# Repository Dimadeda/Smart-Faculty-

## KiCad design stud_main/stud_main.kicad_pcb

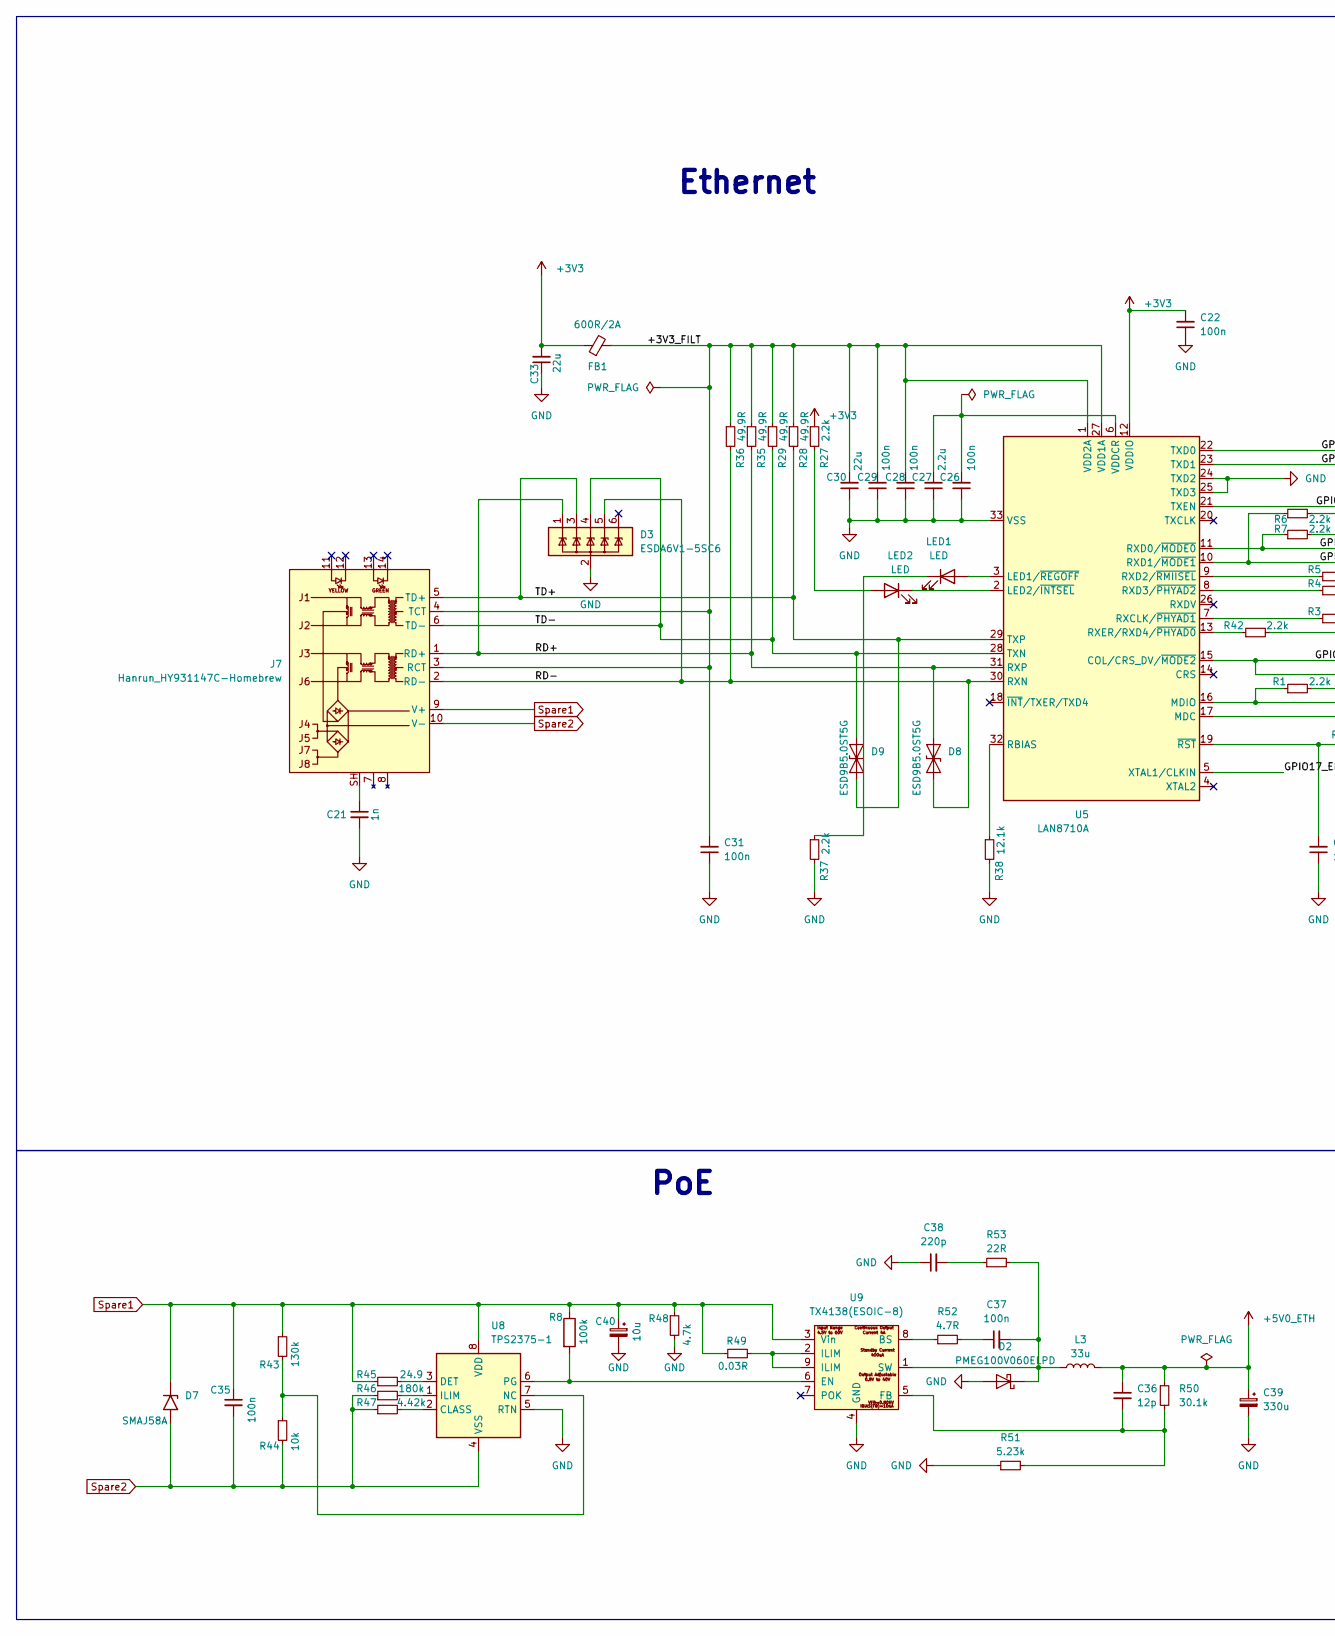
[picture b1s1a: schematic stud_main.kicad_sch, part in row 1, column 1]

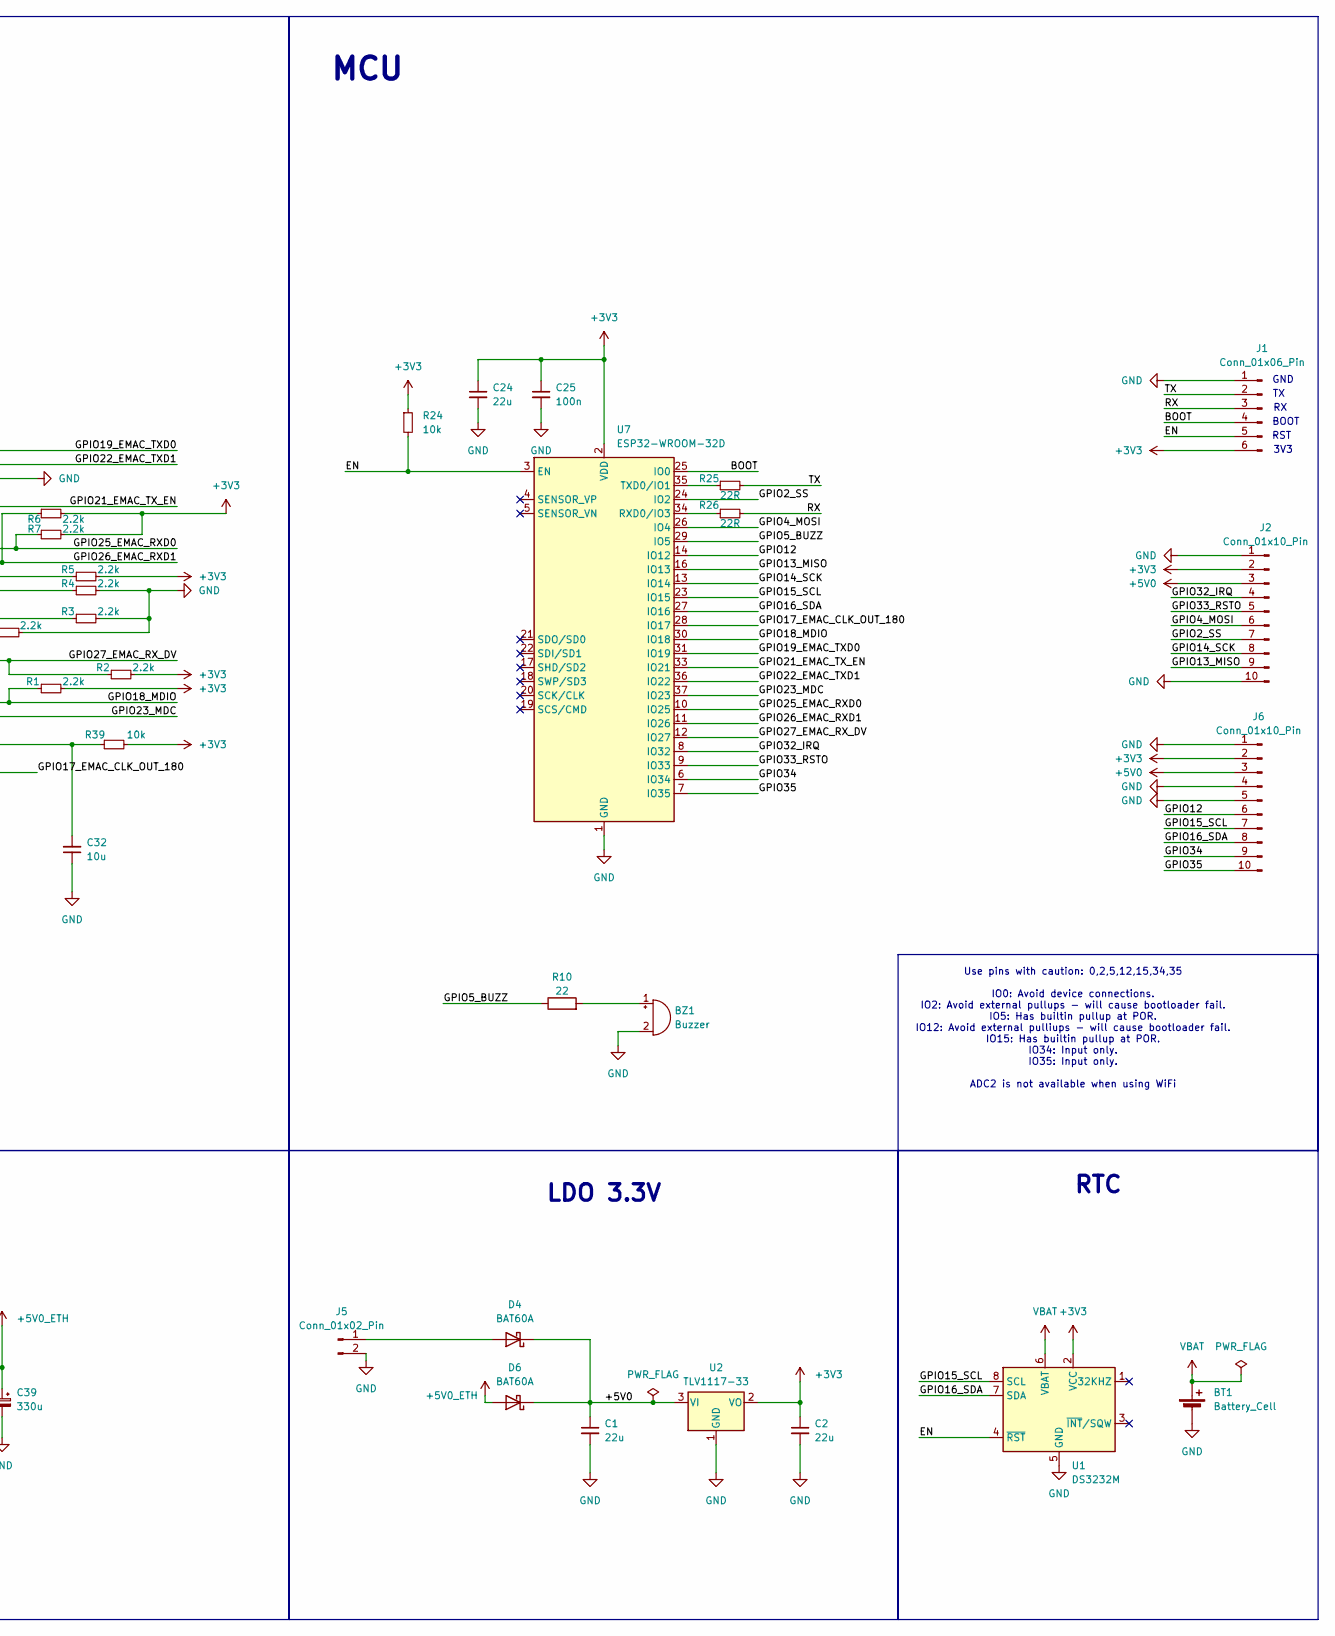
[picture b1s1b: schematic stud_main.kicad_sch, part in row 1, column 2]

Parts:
BT1: Battery_Cell; BatteryHolder_Keystone_1060_1x2032
BZ1: Buzzer; Buzzer_12x9.5RM7.6
C1, C2, C24, C30, C33: 22u; C_0805_2012Metric_Pad1.18x1.45mm_HandSolder
C21: 1n; C_0805_2012Metric_Pad1.18x1.45mm_HandSolder
C22, C25, C26, C28, C29, C35, C37: 100n; C_0805_2012Metric
C27: 2.2u; C_0805_2012Metric_Pad1.18x1.45mm_HandSolder
C31: 100n; C_0805_2012Metric_Pad1.18x1.45mm_HandSolder
C32: 10u; C_0805_2012Metric_Pad1.18x1.45mm_HandSolder
C36: 12p; C_0805_2012Metric_Pad1.18x1.45mm_HandSolder
C38: 220p; C_0805_2012Metric_Pad1.18x1.45mm_HandSolder
C39: 330u; CP_EIA-7343-30_AVX-N_Pad2.25x2.55mm_HandSolder
C40: 10u; C_1210_3225Metric
D2: PMEG100V060ELPD; Nexperia_CFP15_SOT-1289
D3: ESDA6V1-5SC6; SOT-23-6
D4, D6: BAT60A; D_SOD-323
D7: SMAJ58A; D_SMA
D8, D9: ESD9B5.0ST5G; D_SOD-923
FB1: 600R/2A; L_0805_2012Metric
J1: Conn_01x06_Pin; PinHeader_1x06_P2.54mm_Vertical
J2, J6: Conn_01x10_Pin; PinHeader_1x10_P2.54mm_Vertical
J5: Conn_01x02_Pin; PinHeader_1x02_P2.54mm_Vertical
J7: Hanrun_HY931147C-Homebrew; RJ45_Hanrun_HY934711C
L3: 33u; L_Sumida_CDMC6D28_7.25x6.5mm
LED1, LED2: LED; LED_0805_2012Metric
R1, R2, R3, R4, R5, R6, R7, R27, R37, R42: 2.2k; R_0805_2012Metric_Pad1.20x1.40mm_HandSolder
R8: 100k; R_0805_2012Metric_Pad1.20x1.40mm_HandSolder
R10: 22; R_0805_2012Metric
R24, R39, R44: 10k; R_0805_2012Metric_Pad1.20x1.40mm_HandSolder
R25, R26, R53: 22R; R_0805_2012Metric_Pad1.20x1.40mm_HandSolder
R28, R29, R35, R36: 49.9R; R_0805_2012Metric_Pad1.20x1.40mm_HandSolder
R38: 12.1k; R_0805_2012Metric_Pad1.20x1.40mm_HandSolder
R43: 130k; R_0805_2012Metric_Pad1.20x1.40mm_HandSolder
R45: 24.9; R_0805_2012Metric_Pad1.20x1.40mm_HandSolder
R46: 180k; R_0805_2012Metric_Pad1.20x1.40mm_HandSolder
R47: 4.42k; R_0805_2012Metric_Pad1.20x1.40mm_HandSolder
R48: 4.7k; R_1812_4532Metric_Pad1.30x3.40mm_HandSolder
R49: 0.03R; R_1206_3216Metric_Pad1.30x1.75mm_HandSolder
R50: 30.1k; R_0805_2012Metric_Pad1.20x1.40mm_HandSolder
R51: 5.23k; R_0805_2012Metric_Pad1.20x1.40mm_HandSolder
R52: 4.7R; R_0805_2012Metric_Pad1.20x1.40mm_HandSolder
U1: DS3232M; SOIC-8_3.9x4.9mm_P1.27mm
U2: TLV1117-33; SOT-223-3_TabPin2
U5: LAN8710A; QFN-32-1EP_5x5mm_P0.5mm_EP3.3x3.3mm_ThermalVias
U7: ESP32-WROOM-32D
U8: TPS2375-1; TSSOP-8_4.4x3mm_P0.65mm
U9: TX4138(ESOIC-8); SOIC-8-1EP_3.9x4.9mm_P1.27mm_EP2.41x3.3mm

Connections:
+3V3: C2.1, C22.2, C24.1, C25.1, C33.2, FB1.1, J1.6, J2.2, J6.2, R1.2, R2.2, R5.2, R6.2, R7.2, R24.1, R27.1, R39.2, U1.2 (VCC), U2.2 (VO), U5.12 (VDDIO), U7.2 (VDD)
+5V0: C1.1, D4.1 (K), D6.1 (K), J2.3, J6.3, U2.3 (VI)
+5V0_ETH: C36.1, C39.1, D6.2 (A), L3.2, R50.1
/+3V3_FILT: C28.2, C29.2, C30.2, C31.2, FB1.2, J7.3 (RCT), J7.4 (TCT), R28.1, R29.1, R35.1, R36.1, U5.1 (VDD2A), U5.27 (VDD1A)
/BOOT: J1.4, U7.25 (IO0)
/EN: J1.5, R24.2, U1.4 (~RST), U7.3 (EN)
/GPIO2_SS: J2.7, U7.24 (IO2)
/GPIO4_MOSI: J2.6, U7.26 (IO4)
/GPIO5_BUZZ: R10.1, U7.29 (IO5)
/GPIO12: J6.6, U7.14 (IO12)
/GPIO13_MISO: J2.9, U7.16 (IO13)
/GPIO14_SCK: J2.8, U7.13 (IO14)
/GPIO15_SCL: J6.7, U1.8 (SCL), U7.23 (IO15)
/GPIO16_SDA: J6.8, U1.7 (SDA), U7.27 (IO16)
/GPIO17_EMAC_CLK_OUT_180: U5.5 (XTAL1/CLKIN), U7.28 (IO17)
/GPIO18_MDIO: R1.1, U5.16 (MDIO), U7.30 (IO18)
/GPIO19_EMAC_TXD0: U5.22 (TXD0), U7.31 (IO19)
/GPIO21_EMAC_TX_EN: U5.21 (TXEN), U7.33 (IO21)
/GPIO22_EMAC_TXD1: U5.23 (TXD1), U7.36 (IO22)
/GPIO23_MDC: U5.17 (MDC), U7.37 (IO23)
/GPIO25_EMAC_RXD0: R7.1, U5.11 (RXD0/~MODE0), U7.10 (IO25)
/GPIO26_EMAC_RXD1: R6.1, U5.10 (RXD1/~MODE1), U7.11 (IO26)
/GPIO27_EMAC_RX_DV: R2.1, U5.15 (COL/CRS_DV/~MODE2), U7.12 (IO27)
/GPIO32_IRQ: J2.4, U7.8 (IO32)
/GPIO33_RSTO: J2.5, U7.9 (IO33)
/GPIO34: J6.9, U7.6 (IO34)
/GPIO35: J6.10, U7.7 (IO35)
/RD+: D3.1 (IO1), D8.2 (A2), J7.1 (RD+), R35.2, U5.31 (RXP)
/RD-: D3.5 (IO4), D8.1 (A1), J7.2 (RD-), R36.2, U5.30 (RXN)
/RX: J1.3, R26.2
/TD+: D3.3 (IO2), D9.2 (A2), J7.5 (TD+), R28.2, U5.29 (TXP)
/TD-: D3.4 (IO3), D9.1 (A1), J7.6 (TD-), R29.2, U5.28 (TXN)
/TX: J1.2, R25.2
GND: BT1.2 (-), BZ1.2 (-), C1.2, C2.2, C21.2, C22.1, C24.2, C25.2, C26.1, C27.1, C28.1, C29.1, C30.1, C31.1, C32.1, C33.1, C38.1, C39.2, C40.2, D2.1 (A), D2.2 (A), D3.2 (GND), J1.1, J2.1, J2.10, J5.2, J6.1, J6.4, J6.5, R3.2, R4.2, R37.2, R38.2, R42.2, R48.2, R51.1, U1.5 (GND), U2.1 (GND), U5.24 (TXD2), U5.25 (TXD3), U5.33 (VSS), U7.1 (GND), U7.15 (GND), U7.38 (GND), U7.39 (GND), U8.5 (RTN), U9.4 (GND)
unnamed: BZ1.1 (+), R10.2
unnamed: C21.1, J7.SH
unnamed: C37.1, R52.2
unnamed: C38.2, R53.1
unnamed: C37.2, D2.3 (K), L3.1, R53.2, U9.1 (SW)
unnamed: D4.2 (A), J5.1
unnamed: LED1.2 (A), U5.3 (LED1/~REGOFF)
unnamed: LED1.1 (K), R37.1
unnamed: LED2.2 (A), R27.2
unnamed: LED2.1 (K), U5.2 (LED2/~INTSEL)
unnamed: R49.2, U9.2 (ILIM), U9.9 (ILIM)
unnamed: R38.1, U5.32 (RBIAS)
unnamed: R3.1, U5.7 (RXCLK/~PHYAD1)
unnamed: R5.1, U5.9 (RXD2/~RMIISEL)
unnamed: R4.1, U5.8 (RXD3/~PHYAD2)
unnamed: R42.1, U5.13 (RXER/RXD4/~PHYAD0)
unnamed: C26.2, C27.2, U5.6 (VDDCR)
unnamed: C32.2, R39.1, U5.19 (~RST)
unnamed: R26.1, U7.34 (RXD0/IO3)
unnamed: R25.1, U7.35 (TXD0/IO1)
unnamed: R47.2, U8.2 (CLASS)
unnamed: R45.2, U8.3 (DET)
unnamed: R46.2, U8.1 (ILIM)
unnamed: R43.2, R44.1, U8.7 (NC)
unnamed: R8.2, U8.6 (PG), U9.6 (EN)
unnamed: R52.1, U9.8 (BS)
unnamed: C36.2, R50.2, R51.2, U9.5 (FB)
Spare1: C35.1, C40.1, D7.1 (A1), J7.9 (V+), R8.1, R43.1, R45.1, R48.1, R49.1, U8.8 (VDD), U9.3 (Vin)
Spare2: C35.2, D7.2 (A2), J7.10 (V-), R44.2, R46.1, R47.1, U8.4 (VSS)
VBAT: BT1.1 (+), U1.6 (VBAT)

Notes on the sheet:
3V3
BOOT
Use pins with caution: 0,2,5,12,15,34,35 IO0: Avoid device connections. IO2: Avoid external pullups - will cause bootloader fail. IO5: Has builtin pullup at POR. IO12: Avoid external pulliups - will cause bootloader fail. IO15: Has builtin pullup at POR. IO34: Input only. IO35: Input only. ADC2 is 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
RST
MCU
Ethernet
GND
LDO 3.3V
RTC
PoE

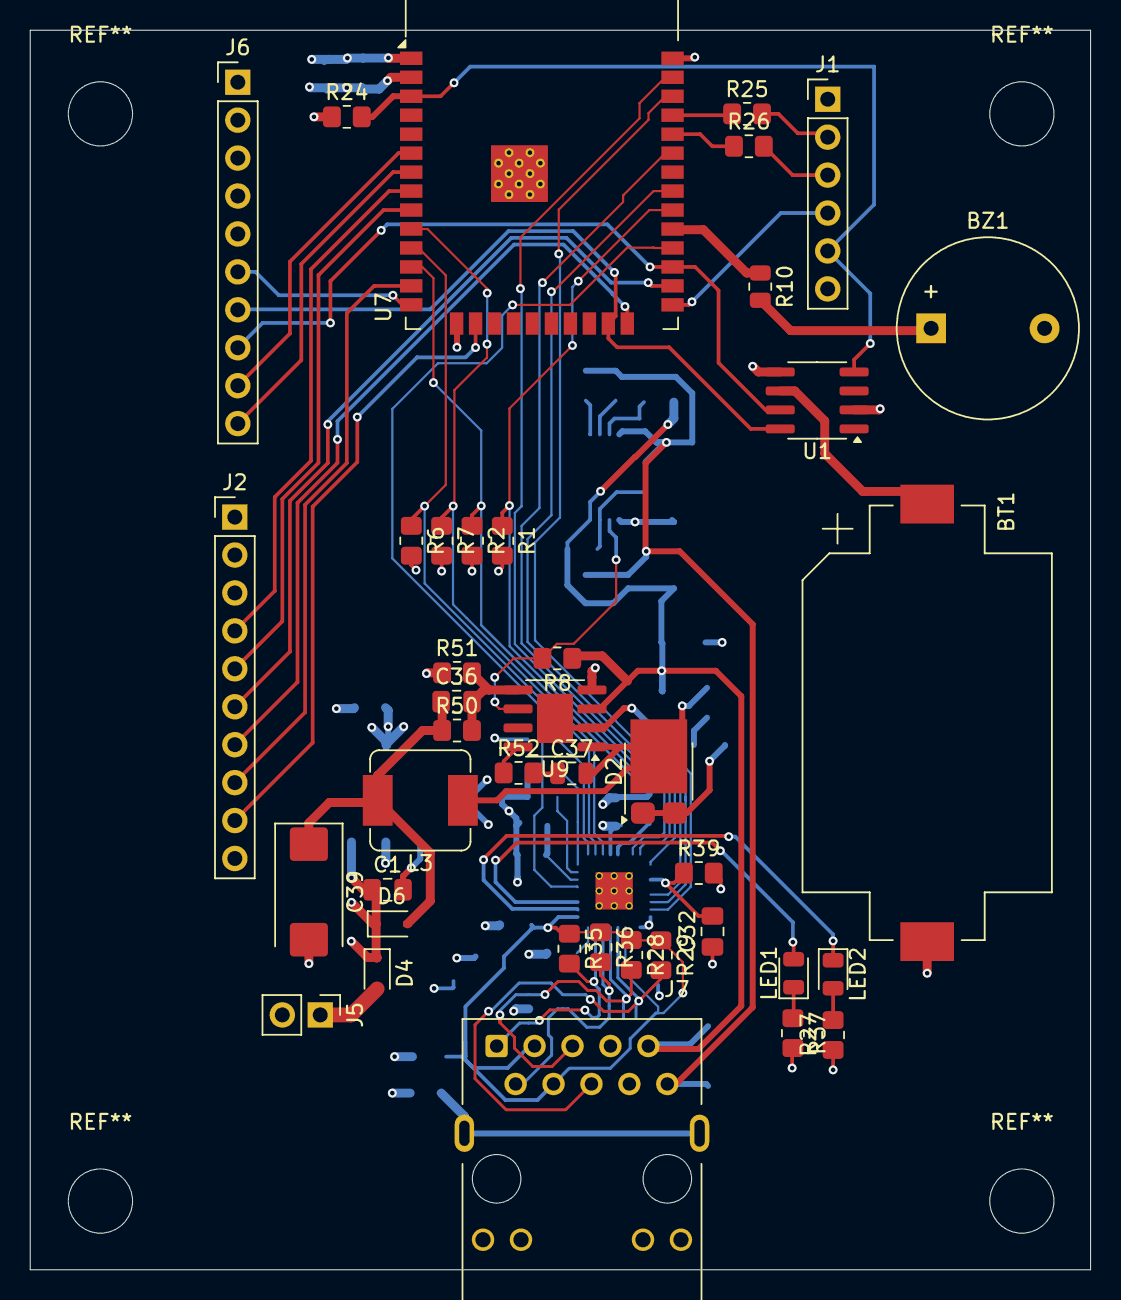
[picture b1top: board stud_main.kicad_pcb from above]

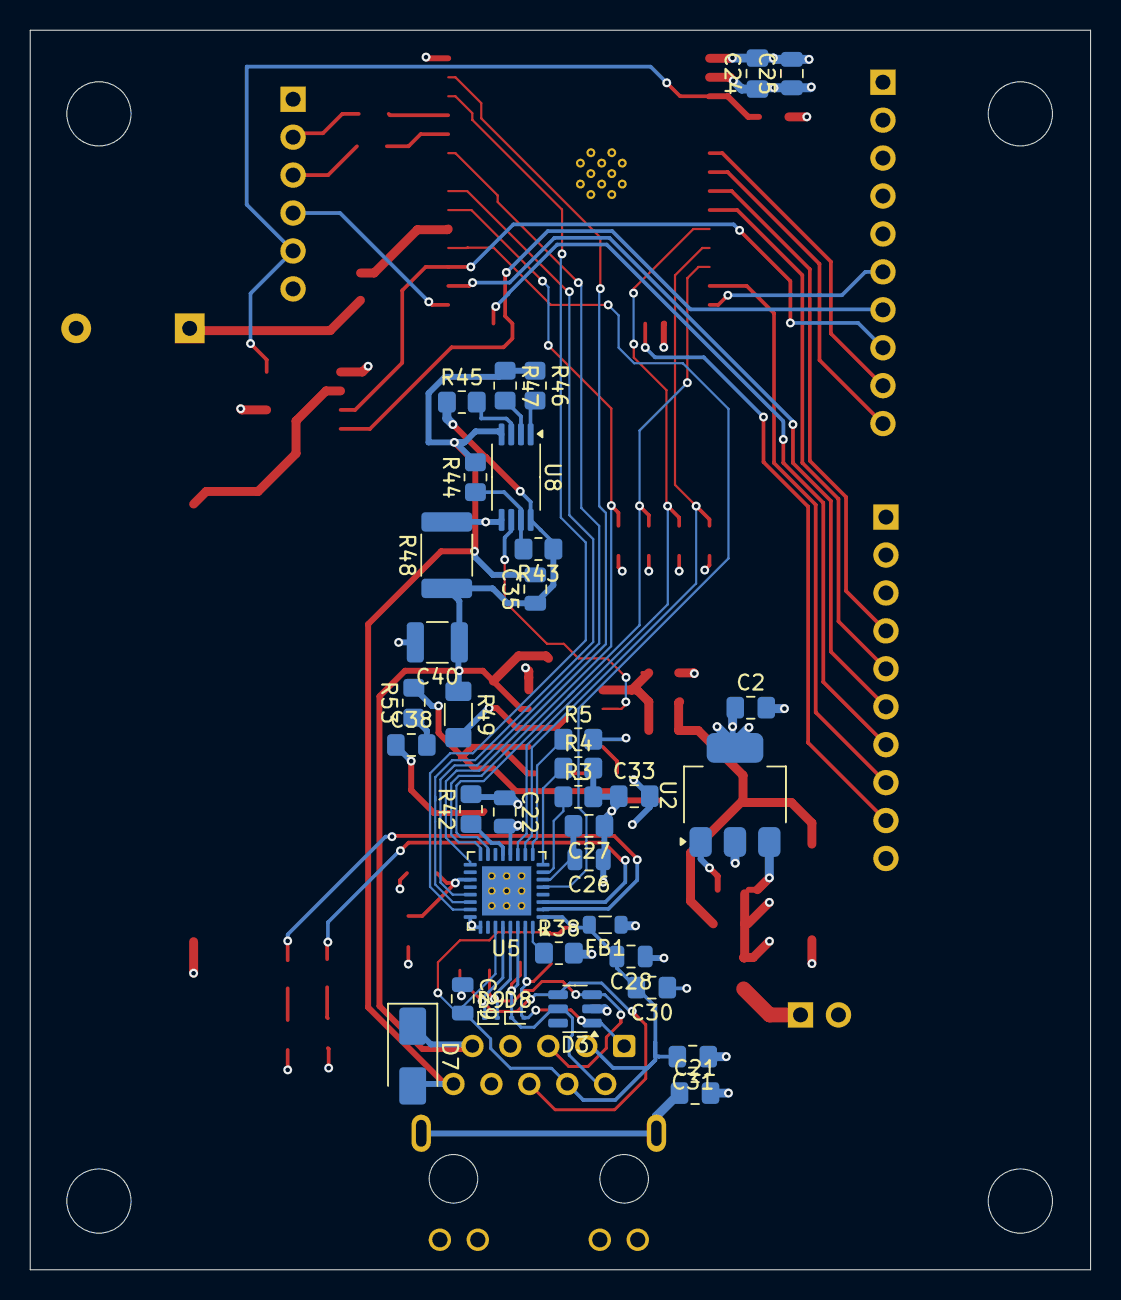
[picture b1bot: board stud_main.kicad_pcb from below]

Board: 4 copper layers, 71.0 x 83.0 mm, 76 parts (36 on the bottom side), 64 nets.
